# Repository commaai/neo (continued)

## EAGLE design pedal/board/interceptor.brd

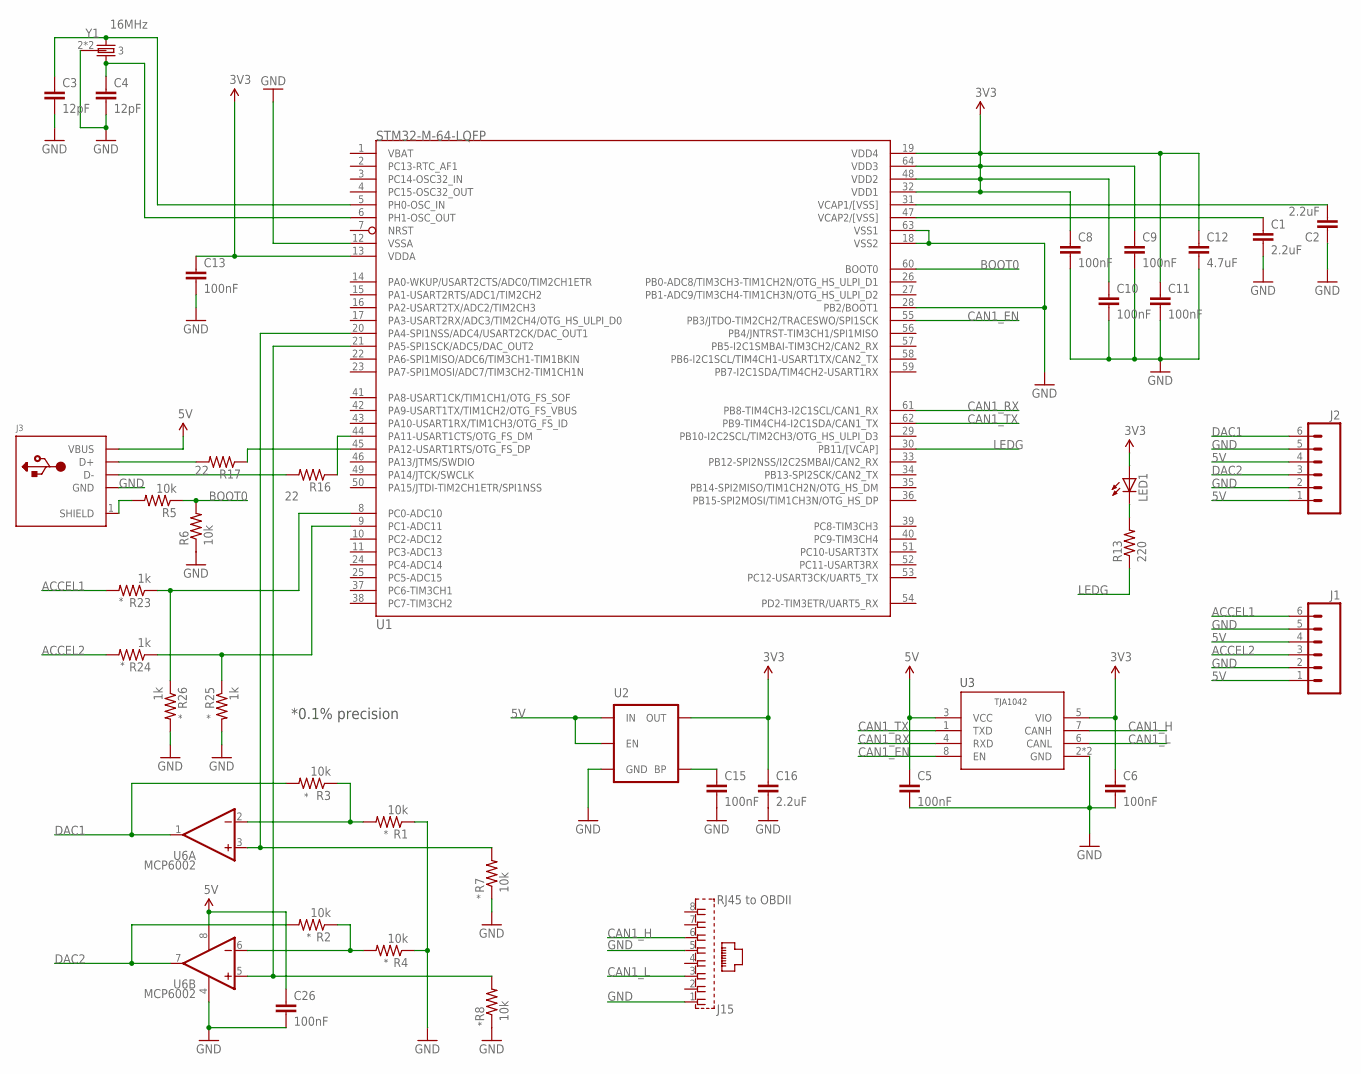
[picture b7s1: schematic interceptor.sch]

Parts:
C1, C2, C16: 2.2uF; 0603-C
C3, C4: 12pF; 0603-C
C5, C6, C8, C9, C10, C11, C13, C15, C26: 100nF; 0603-C
C12: 4.7uF; 0603-C
J1, J2: M06NO_SILK_YES_STOP; 1X06_NO_SILK_YES_STOP
J3: USB-ASMD-F; USB-A-S
J15: RJ45 to OBDII; RA-RJ45
LED1: LEDCHIPLED_0805; CHIPLED_0805
R1, R2, R3, R4, R5, R6, R7, R8: 10k; 0402-R
R13: 220; 0402-R
R16, R17: 22; 0402-R
R23, R24, R25, R26: 1k; 0402-R
U1: STM32-M-64-LQFP; LQFP64
U2: MIC52053.3V; SOT23-5
U3: TJA1042HVSON; HVSON8
U6: MCP6002; SO08
Y1: 16MHz; XTAL-3.2X2.5

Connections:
3V3: C6.1, C8.1, C9.1, C10.1, C11.1, C12.1, C13.1, C16.1, LED1.A, U1.13 (VDDA), U1.19 (VDD4), U1.32 (VDD1), U1.48 (VDD2), U1.64 (VDD3), U2.5 (OUT), U3.5 (VIO)
5V: C5.1, C26.1, J1.1, J1.4, J2.1, J2.4, J3.VBUS, U2.1 (IN), U2.3 (EN), U3.3 (VCC), U6.8 (V+)
ACCEL1: J1.6, R23.2
ACCEL2: J1.3, R24.2
BOOT0: R5.1, R6.2, U1.60 (BOOT0)
CAN1_EN: U1.55 (PB3/JTDO-TIM2CH2/TRACESWO/SPI1SCK), U3.8 (EN)
CAN1_H: J15.6, U3.7 (CANH)
CAN1_L: J15.3, U3.6 (CANL)
CAN1_RX: U1.61 (PB8-TIM4CH3-I2C1SCL/CAN1_RX), U3.4 (RXD)
CAN1_TX: U1.62 (PB9-TIM4CH4-I2C1SDA/CAN1_TX), U3.1 (TXD)
DAC1: J2.6, R3.2, U6.1 (OUT)
DAC2: J2.3, R2.2, U6.7 (OUT)
GND: C1.2, C2.1, C3.2, C4.2, C5.2, C6.2, C8.2, C9.2, C10.2, C11.2, C12.2, C13.2, C15.2, C16.2, C26.2, J1.2, J1.5, J2.2, J2.5, J3.GND, J15.1, J15.5, R1.1, R4.1, R6.1, R7.1, R8.1, R25.2, R26.2, U1.12 (VSSA), U1.18 (VSS2), U1.28 (PB2/BOOT1), U1.63 (VSS1), U2.2 (GND), U3.2 (GND), U3.PAD (GND), U6.4 (V-), Y1.2 (3), Y1.4 (3)
LEDG: R13.1, U1.30 (PB11/[VCAP])
unnamed: C3.1, U1.5 (PH0-OSC_IN), Y1.1
unnamed: R16.1, U1.44 (PA11-USART1CTS/OTG_FS_DM)
unnamed: C4.1, U1.6 (PH1-OSC_OUT), Y1.3 (2)
unnamed: R17.1, U1.45 (PA12-USART1RTS/OTG_FS_DP)
unnamed: J3.D-, R16.2
unnamed: J3.D+, R17.2
unnamed: J3.1 (SHIELD), R5.2
unnamed: R7.2, U1.20 (PA4-SPI1NSS/ADC4/USART2CK/DAC_OUT1), U6.3 (+IN)
unnamed: R8.2, U1.21 (PA5-SPI1SCK/ADC5/DAC_OUT2), U6.5 (+IN)
unnamed: R1.2, R3.1, U6.2 (-IN)
unnamed: R2.1, R4.2, U6.6 (-IN)
unnamed: LED1.C, R13.2
unnamed: C15.1, U2.4 (BP)
unnamed: R23.1, R26.1, U1.8 (PC0-ADC10)
unnamed: R24.1, R25.1, U1.9 (PC1-ADC11)
VCAP1: C2.2, U1.31 (VCAP1/[VSS])
VCAP2: C1.1, U1.47 (VCAP2/[VSS])

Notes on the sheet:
*0.1% precision

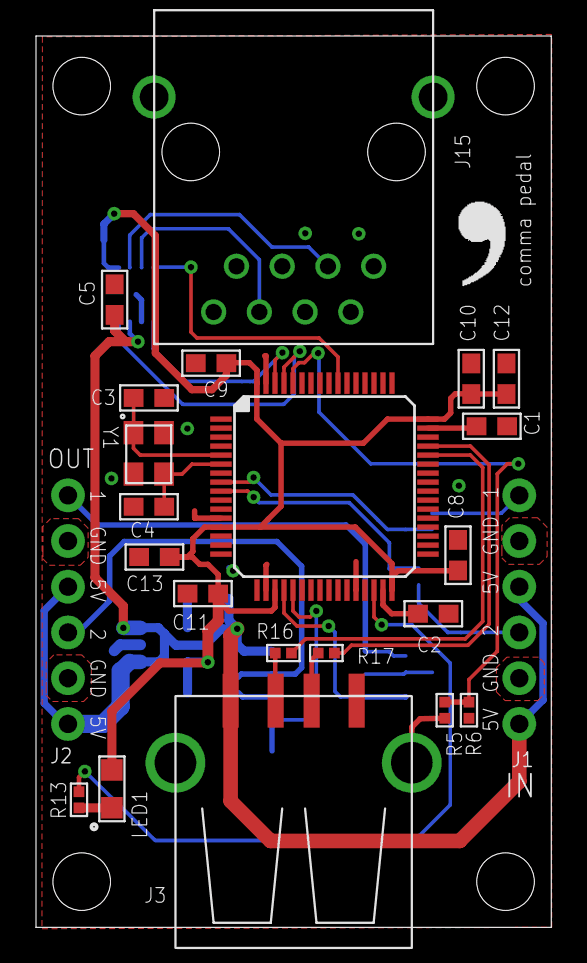
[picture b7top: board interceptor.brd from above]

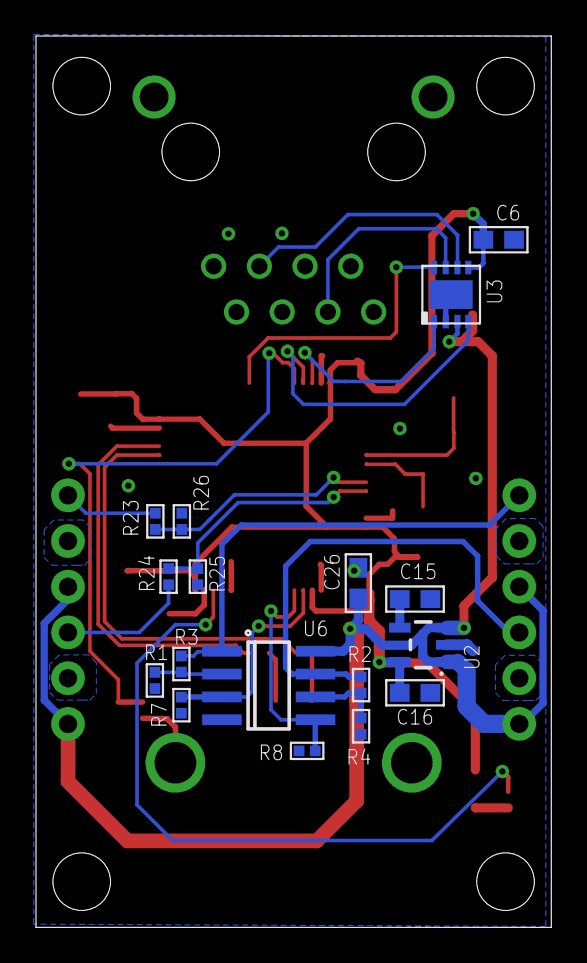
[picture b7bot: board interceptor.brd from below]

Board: 2 copper layers, 28.6 x 49.5 mm, 41 parts (17 on the bottom side), 31 nets.

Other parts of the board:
U$1: LOGO

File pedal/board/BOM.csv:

Ref Des,Value,Package,Qty,MPN,Link
"C1, C2, C16",2.2uF,0603-C,3,EMK107BJ225KA-T,
C12,4.7uF,0603-C,1,CL10B475KQ8NQNC,
"C3, C4",12pF,0603-C,2,C1608C0G1H120J080AA,
"C5, C6, C8, C9, C10, C11, C13, C15, C26",100nF,0603-C,9,GCM188R71C104KA37D,
"J1, J2",-,1X06_NO_SILK_YES_STOP,2,-,
J15,RJ45,RA-RJ45,1,A-2004-2-4-LPS-N-R,
J3,USB-ASMD-F,USB-A-S,1,87583-2010BLF,
J4,HONDA-6PIN,,1,HONDA-6PIN,https://www.aliexpress.com/item/Female-Male-6-Pin-Electrical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
LED1,GREEN,CHIPLED_0805,1,LG R971-KN-1,
"R1, R2, R3, R4, R7, R8","10k, 0.1%",0402-R,6,ERA-2AEB103X,
R13,220,0402-R,1,RC0402FR-07220RL,
"R16, R17",22,0402-R,2,RC0402FR-0722RL,
"R23, R24, R25, R26","1k, 0.1%",0402-R,4,ERA-2AEB102X,
"R5, R6",10k,0402-R,2,RC0402JR-0710KL,
U1,STM32-M-64-LQFP,LQFP64,1,STM32F205RET6,
U2,3V3,SOT23-5,1,TPS73433TDDCRQ1,
U3,TJA1042HVSON,HVSON8,1,TJA1042TK/3/1J,
U6,MCP6002,SO08,1,MCP6002T-I/SN,
Y1,16MHz,XTAL-3.2X2.5,1,ABM8AIG-16.000MHZ-12-2Z-T3,
